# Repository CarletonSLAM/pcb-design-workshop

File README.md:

# Arduino Clone - PCB Workshop

EAGLE CAD project files for IEEE Carleton University PCB Design Workshops.

(c) Hasith Vidanamadura, 2015
(c) Irusha Vidanamadura and Maryam Kaka, 2017

### License

This is a MIT-licensed project.

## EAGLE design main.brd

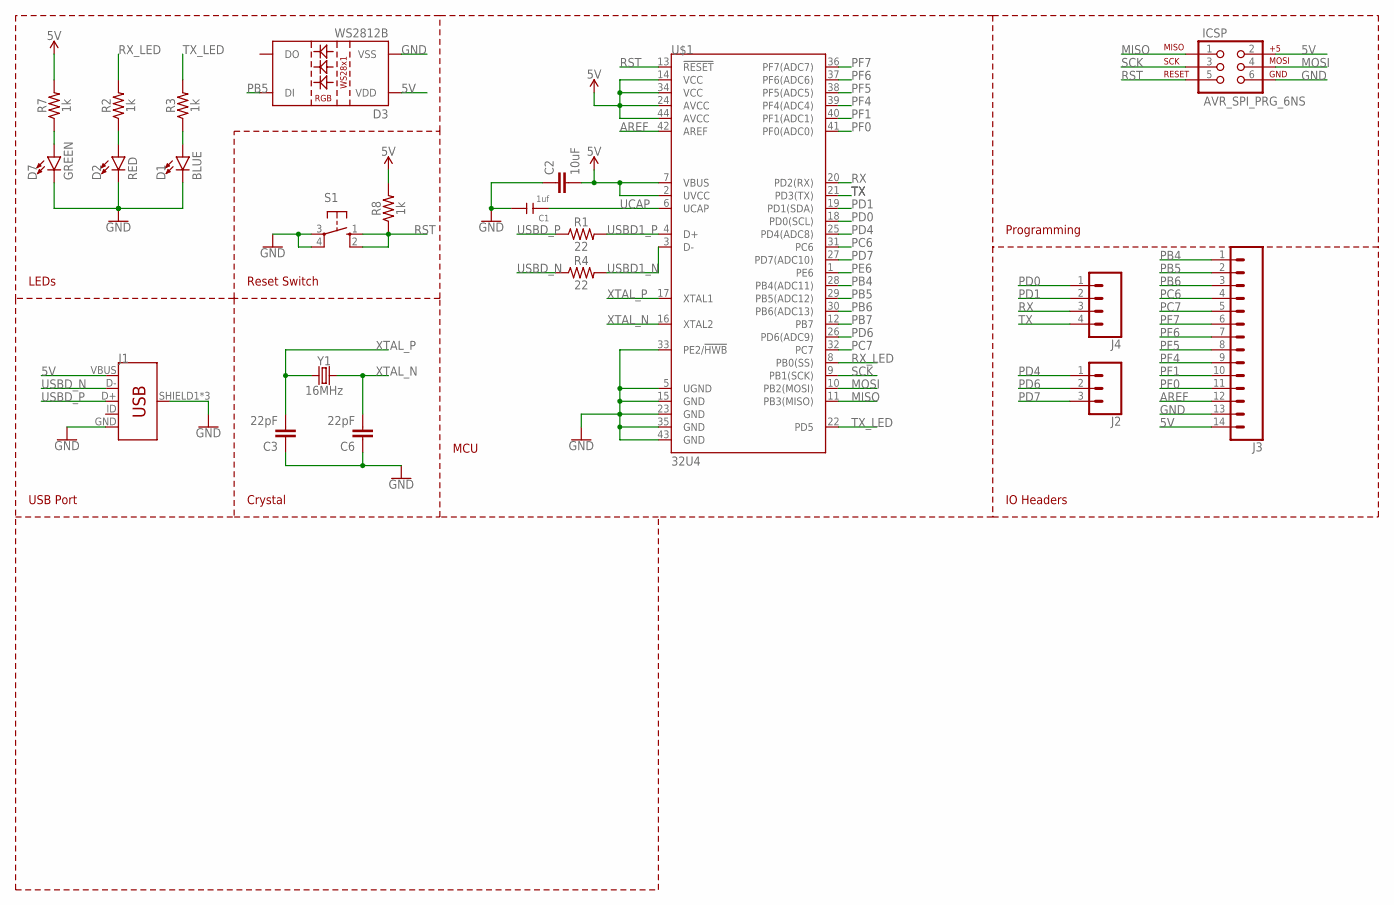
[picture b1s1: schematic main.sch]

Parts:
C1: 1uf; C0603
C2: 10uF; 0805
C3, C6: 22pF; 0603
D1: BLUE; LED-0603
D2: RED; LED-0603
D3: WS2812B
D7: GREEN; LED-0603
ICSP: AVR_SPI_PRG_6NS; 2X3-NS
J1: USB_MICRO-B_FEMALE-SMT; USB-B-MICRO-SMD
J2: CONN_03; 1X03
J3: CONN_14; 1X14
J4: CONN_04; 1X04
R1, R4: 22; 0603
R2, R3, R7, R8: 1k; 0805
S1: 10-XX; B3F-10XX
U$1: 32U4; TQFP44
Y1: 16MHz; HC49US

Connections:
5V: C2.2, D3.1 (VDD), ICSP.2, J1.VBUS, J3.14, R7.2, R8.2, U$1.2 (UVCC), U$1.7 (VBUS), U$1.14 (VCC), U$1.24 (AVCC), U$1.34 (VCC), U$1.44 (AVCC)
AREF: J3.12, U$1.42 (AREF)
GND: C1.2, C2.1, C3.1, C6.1, D1.C, D2.C, D3.3 (VSS), D7.C, ICSP.6, J1.GND, J1.SHIELD1 (SHIELD), J1.SHIELD2 (SHIELD), J1.SHIELD3 (SHIELD), J3.13, S1.3, S1.4 (P1), U$1.5 (UGND), U$1.15 (GND), U$1.23 (GND), U$1.33 (PE2/!HWB), U$1.35 (GND), U$1.43 (GND)
MISO: ICSP.1, U$1.11 (PB3(MISO))
MOSI: ICSP.4, U$1.10 (PB2(MOSI))
unnamed: D1.A, R3.1
unnamed: D2.A, R2.1
unnamed: D7.A, R7.1
PB4: J3.1, U$1.28 (PB4(ADC11))
PB5: D3.4 (DI), J3.2, U$1.29 (PB5(ADC12))
PB6: J3.3, U$1.30 (PB6(ADC13))
PB7: U$1.12 (PB7)
PC6: J3.4, U$1.31 (PC6)
PC7: J3.5, U$1.32 (PC7)
PD0: J4.1, U$1.18 (PD0(SCL))
PD1: J4.2, U$1.19 (PD1(SDA))
PD4: J2.1, U$1.25 (PD4(ADC8))
PD6: J2.2, U$1.26 (PD6(ADC9))
PD7: J2.3, U$1.27 (PD7(ADC10))
PE6: U$1.1 (PE6)
PF0: J3.11, U$1.41 (PF0(ADC0))
PF1: J3.10, U$1.40 (PF1(ADC1))
PF4: J3.9, U$1.39 (PF4(ADC4))
PF5: J3.8, U$1.38 (PF5(ADC5))
PF6: J3.7, U$1.37 (PF6(ADC6))
PF7: J3.6, U$1.36 (PF7(ADC7))
RST: ICSP.5, R8.1, S1.1 (S), S1.2 (S1), U$1.13 (!RESET)
RX: J4.3, U$1.20 (PD2(RX))
RX_LED: R2.2, U$1.8 (PB0(SS))
SCK: ICSP.3, U$1.9 (PB1(SCK))
TX: J4.4, U$1.21 (PD3(TX))
TX_LED: R3.2, U$1.22 (PD5)
UCAP: C1.1, U$1.6 (UCAP)
USBD1_N: R4.2, U$1.3 (D-)
USBD1_P: R1.2, U$1.4 (D+)
USBD_N: J1.D-, R4.1
USBD_P: J1.D+, R1.1
XTAL_N: C6.2, U$1.16 (XTAL2), Y1.2
XTAL_P: C3.2, U$1.17 (XTAL1), Y1.1

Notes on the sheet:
Programming
IO Headers
MCU
LEDs
USB Port
Reset Switch
Crystal

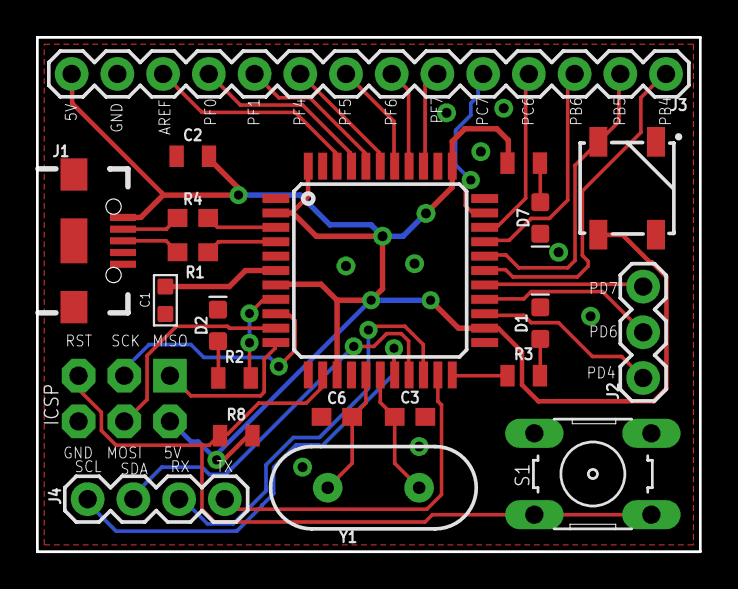
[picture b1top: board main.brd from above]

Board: 2 copper layers, 36.8 x 28.6 mm, 22 parts (0 on the bottom side), 37 nets.

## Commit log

2015-09-14 Initial commit with all EAGLE files.
2015-09-26 Work in progress commit for r1.1
    1. Changed VREG to smaller package
    2. Added RST decoupling capacitor
    3. Added idiot diode
    4. Removed motor controller and support circuitry.
    5. Added additional decoupling capacitor
    6. Reworked board outline
2017-02-21 Added UART-USB Chip
2017-06-25 Board layout made
2017-06-25 Diff lines routed
2017-06-25 ROutes RX and TX
2017-06-25 Autorouted
2017-06-26 Fixed DRC Errors
2017-07-25 Changes LED drivers to CBUS0 and CBUS1
2017-08-01 8/1/17 - Used new ATMEGA32U4
2017-08-01 Move vias
2017-08-01 AutoRouter +Text
2017-08-01 Added Gerber Files
2017-08-01 Gerber file re process
2017-08-01 Added bom

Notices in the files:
parts and their libraries:
SparkFun-Capacitors: Licensing: Creative Commons ShareAlike 4.0 International - https://creativecommons.org/licenses/by-sa/4.0
